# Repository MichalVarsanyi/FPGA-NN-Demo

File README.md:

# FPGA-NN-Demo

### **⚠️ This project is not final and is still in the development phase ⚠️**

This is a small demo board showing how to compile neural networks (NN) on Xilinx/AMD FPGAs using the hls4ml framework. The board features a 5x5 grid of buttons, where the user can draw a numeral, which gets passed to the fully-connected NN running on the FPGA. Based on the input, the NN infers what numeral the user drew and displays it on the 7-segment display visible at the bottom of the PCB.

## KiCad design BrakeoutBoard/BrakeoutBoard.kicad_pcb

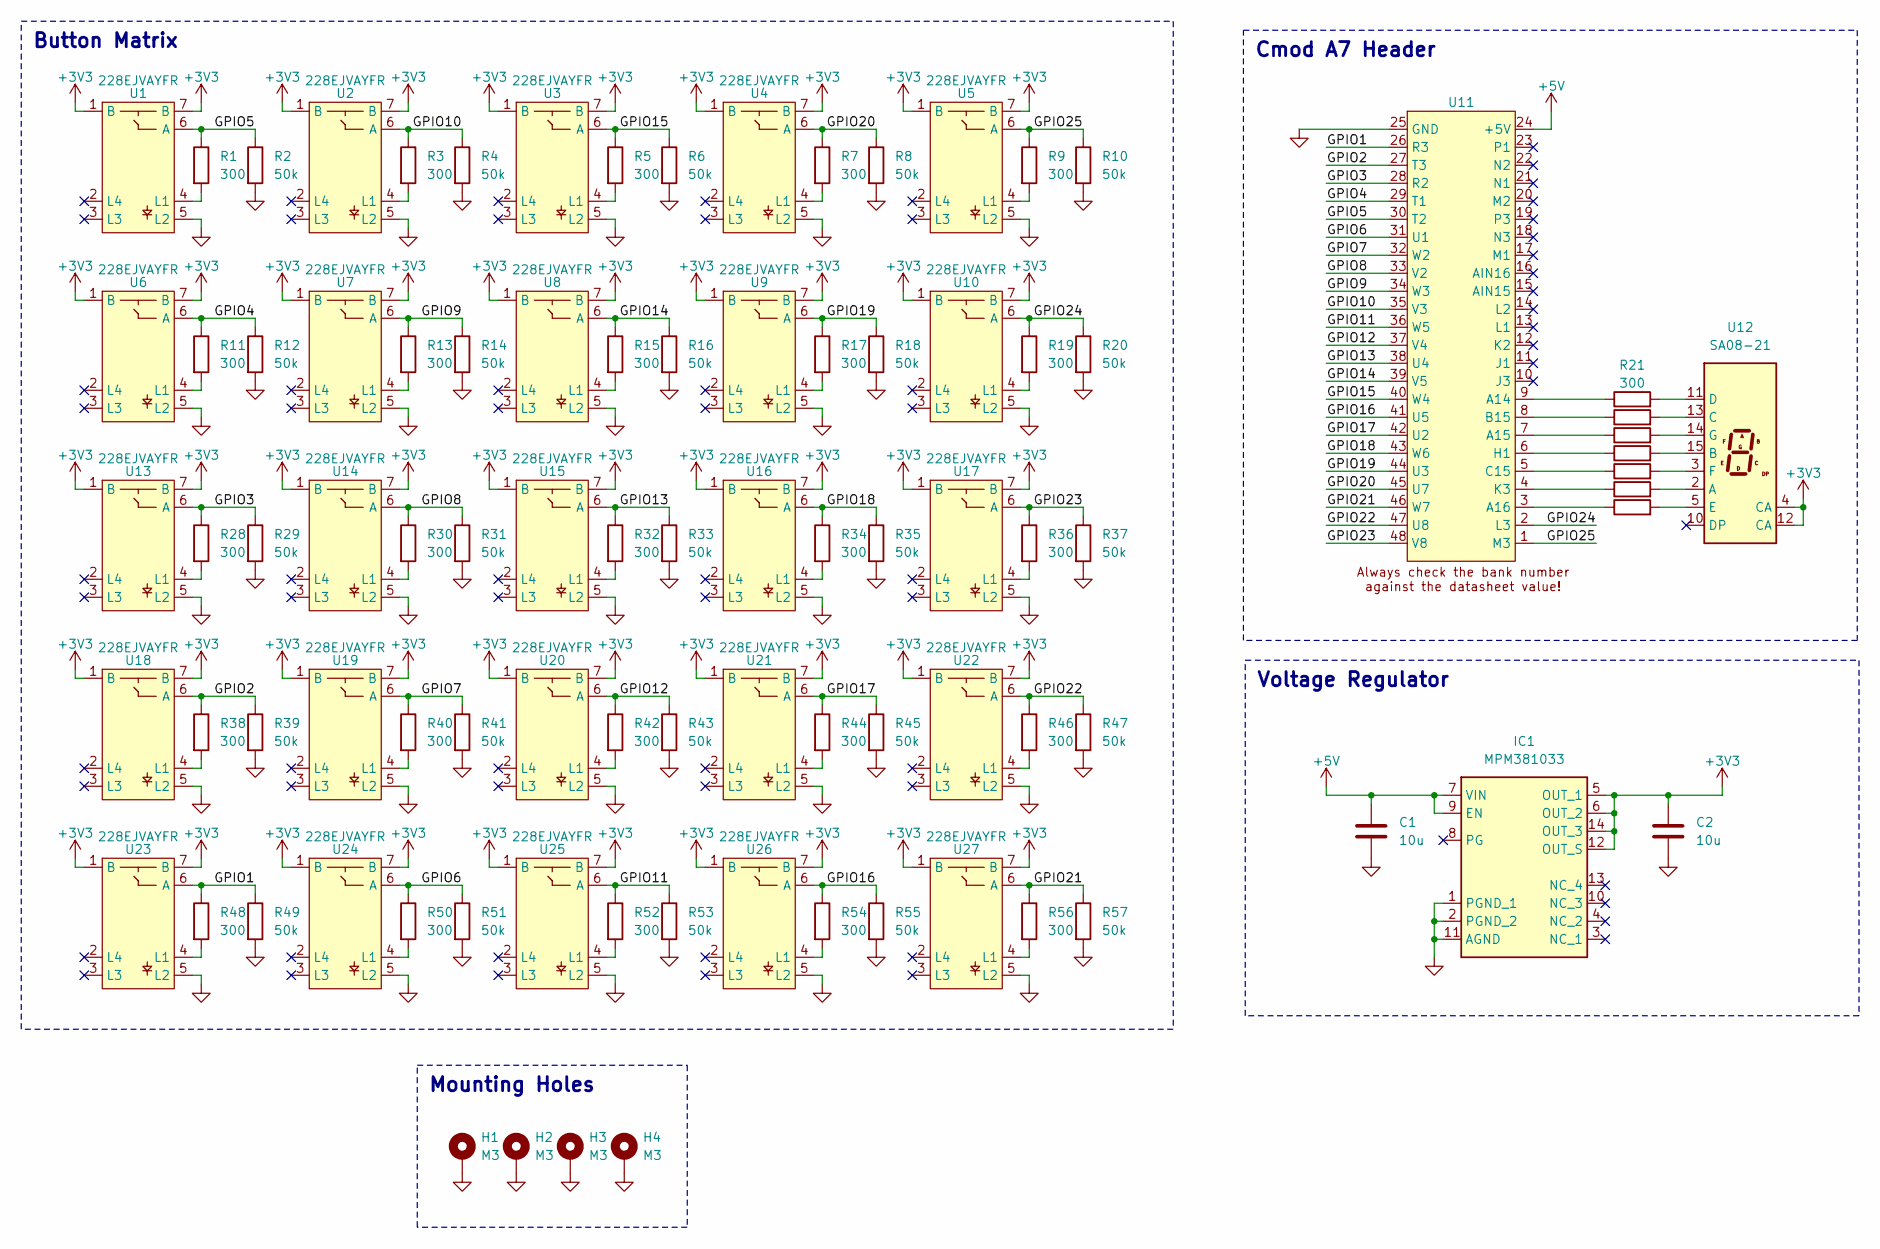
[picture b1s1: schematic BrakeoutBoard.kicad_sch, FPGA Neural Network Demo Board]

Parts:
C1, C2: 10u; C_0805_2012Metric
H1, H2, H3, H4: M3; MountingHole_3.2mm_M3_Pad_Via
IC1: MPM381033; MPM3810GQB33Z; Mouser Part Number 946-MPM3810GQB-33-Z
R1, R3, R5, R7, R9, R11, R13, R15, R17, R19, R21, R22, R23, R24, R25, R26, R27, R28, R30, R32, R34, R36, R38, R40, R42, R44, R46, R48, R50, R52, R54, R56: 300; R_0603_1608Metric
R2, R4, R6, R8, R10, R12, R14, R16, R18, R20, R29, R31, R33, R35, R37, R39, R41, R43, R45, R47, R49, R51, R53, R55, R57: 50k; R_0603_1608Metric
U1, U2, U3, U4, U5, U6, U7, U8, U9, U10, U13, U14, U15, U16, U17, U18, U19, U20, U21, U22, U23, U24, U25, U26, U27: 228EJVAYFR
U11: Cmod_A7
U12: SA08-21; SA08-21SURKWA

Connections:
+3V3: C2.1, IC1.5 (OUT_1), IC1.6 (OUT_2), IC1.12 (OUT_S), IC1.14 (OUT_3), U1.1 (B), U1.7 (B), U2.1 (B), U2.7 (B), U3.1 (B), U3.7 (B), U4.1 (B), U4.7 (B), U5.1 (B), U5.7 (B), U6.1 (B), U6.7 (B), U7.1 (B), U7.7 (B), U8.1 (B), U8.7 (B), U9.1 (B), U9.7 (B), U10.1 (B), U10.7 (B), U12.4 (CA), U12.12 (CA), U13.1 (B), U13.7 (B), U14.1 (B), U14.7 (B), U15.1 (B), U15.7 (B), U16.1 (B), U16.7 (B), U17.1 (B), U17.7 (B), U18.1 (B), U18.7 (B), U19.1 (B), U19.7 (B), U20.1 (B), U20.7 (B), U21.1 (B), U21.7 (B), U22.1 (B), U22.7 (B), U23.1 (B), U23.7 (B), U24.1 (B), U24.7 (B), U25.1 (B), U25.7 (B), U26.1 (B), U26.7 (B), U27.1 (B), U27.7 (B)
+5V: C1.1, IC1.7 (VIN), IC1.9 (EN), U11.24 (+5V)
/GPIO1: R48.1, R49.1, U11.26 (R3), U23.6 (A)
/GPIO2: R38.1, R39.1, U11.27 (T3), U18.6 (A)
/GPIO3: R28.1, R29.1, U11.28 (R2), U13.6 (A)
/GPIO4: R11.1, R12.1, U6.6 (A), U11.29 (T1)
/GPIO5: R1.1, R2.1, U1.6 (A), U11.30 (T2)
/GPIO6: R50.1, R51.1, U11.31 (U1), U24.6 (A)
/GPIO7: R40.1, R41.1, U11.32 (W2), U19.6 (A)
/GPIO8: R30.1, R31.1, U11.33 (V2), U14.6 (A)
/GPIO9: R13.1, R14.1, U7.6 (A), U11.34 (W3)
/GPIO10: R3.1, R4.1, U2.6 (A), U11.35 (V3)
/GPIO11: R52.1, R53.1, U11.36 (W5), U25.6 (A)
/GPIO12: R42.1, R43.1, U11.37 (V4), U20.6 (A)
/GPIO13: R32.1, R33.1, U11.38 (U4), U15.6 (A)
/GPIO14: R15.1, R16.1, U8.6 (A), U11.39 (V5)
/GPIO15: R5.1, R6.1, U3.6 (A), U11.40 (W4)
/GPIO16: R54.1, R55.1, U11.41 (U5), U26.6 (A)
/GPIO17: R44.1, R45.1, U11.42 (U2), U21.6 (A)
/GPIO18: R34.1, R35.1, U11.43 (W6), U16.6 (A)
/GPIO19: R17.1, R18.1, U9.6 (A), U11.44 (U3)
/GPIO20: R7.1, R8.1, U4.6 (A), U11.45 (U7)
/GPIO21: R56.1, R57.1, U11.46 (W7), U27.6 (A)
/GPIO22: R46.1, R47.1, U11.47 (U8), U22.6 (A)
/GPIO23: R36.1, R37.1, U11.48 (V8), U17.6 (A)
/GPIO24: R19.1, R20.1, U10.6 (A), U11.2 (L3)
/GPIO25: R9.1, R10.1, U5.6 (A), U11.1 (M3)
GND: C1.2, C2.2, H1.1, H2.1, H3.1, H4.1, IC1.1 (PGND_1), IC1.2 (PGND_2), IC1.11 (AGND), R2.2, R4.2, R6.2, R8.2, R10.2, R12.2, R14.2, R16.2, R18.2, R20.2, R29.2, R31.2, R33.2, R35.2, R37.2, R39.2, R41.2, R43.2, R45.2, R47.2, R49.2, R51.2, R53.2, R55.2, R57.2, U1.5 (L2), U2.5 (L2), U3.5 (L2), U4.5 (L2), U5.5 (L2), U6.5 (L2), U7.5 (L2), U8.5 (L2), U9.5 (L2), U10.5 (L2), U11.25 (GND), U13.5 (L2), U14.5 (L2), U15.5 (L2), U16.5 (L2), U17.5 (L2), U18.5 (L2), U19.5 (L2), U20.5 (L2), U21.5 (L2), U22.5 (L2), U23.5 (L2), U24.5 (L2), U25.5 (L2), U26.5 (L2), U27.5 (L2)
unnamed: R1.2, U1.4 (L1)
unnamed: R3.2, U2.4 (L1)
unnamed: R5.2, U3.4 (L1)
unnamed: R7.2, U4.4 (L1)
unnamed: R9.2, U5.4 (L1)
unnamed: R11.2, U6.4 (L1)
unnamed: R13.2, U7.4 (L1)
unnamed: R15.2, U8.4 (L1)
unnamed: R17.2, U9.4 (L1)
unnamed: R19.2, U10.4 (L1)
unnamed: R21.1, U11.9 (A14)
unnamed: R23.1, U11.7 (A15)
unnamed: R27.1, U11.3 (A16)
unnamed: R22.1, U11.8 (B15)
unnamed: R25.1, U11.5 (C15)
unnamed: R24.1, U11.6 (H1)
unnamed: R26.1, U11.4 (K3)
unnamed: R26.2, U12.2 (A)
unnamed: R24.2, U12.15 (B)
unnamed: R22.2, U12.13 (C)
unnamed: R21.2, U12.11 (D)
unnamed: R27.2, U12.5 (E)
unnamed: R25.2, U12.3 (F)
unnamed: R23.2, U12.14 (G)
unnamed: R28.2, U13.4 (L1)
unnamed: R30.2, U14.4 (L1)
unnamed: R32.2, U15.4 (L1)
unnamed: R34.2, U16.4 (L1)
unnamed: R36.2, U17.4 (L1)
unnamed: R38.2, U18.4 (L1)
unnamed: R40.2, U19.4 (L1)
unnamed: R42.2, U20.4 (L1)
unnamed: R44.2, U21.4 (L1)
unnamed: R46.2, U22.4 (L1)
unnamed: R48.2, U23.4 (L1)
unnamed: R50.2, U24.4 (L1)
unnamed: R52.2, U25.4 (L1)
unnamed: R54.2, U26.4 (L1)
unnamed: R56.2, U27.4 (L1)

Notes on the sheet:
Voltage Regulator
Button Matrix
Cmod A7 Header
Mounting Holes

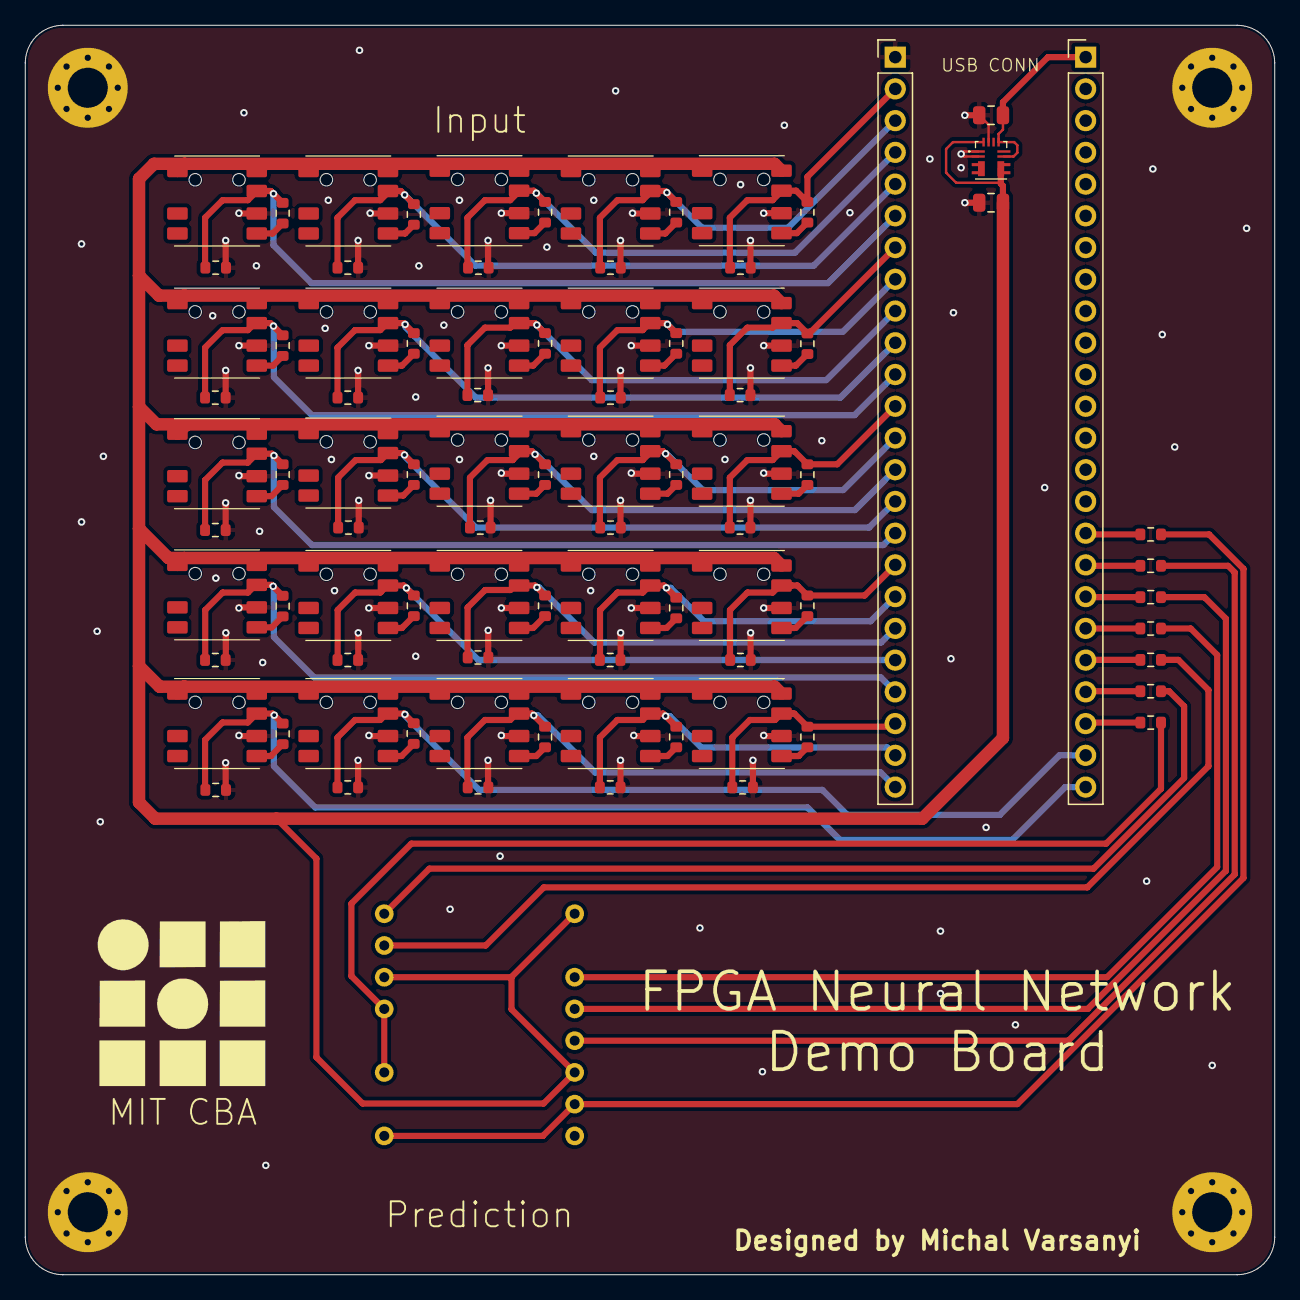
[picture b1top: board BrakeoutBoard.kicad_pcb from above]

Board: 2 copper layers, 100.0 x 100.0 mm, 91 parts (0 on the bottom side), 67 nets.

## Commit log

2026-02-09 Initial commit. Introduced readme and some basic Jupyter notebooks with the code for training and covnerting the NN into RTL.
2026-02-09 Generrated the IP block from the NN
